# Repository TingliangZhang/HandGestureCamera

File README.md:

# HandGestureCamera

## BP相关

主控芯片及PCB上外围电路 约100 其中包括：

| 名称                    | 作用                | 估算BOM价格/RMB |
| ----------------------- | ------------------- | --------------- |
| ESP32-WROOM             | 主控兼Wifi+蓝牙通信 | 13              |
| 网络分析仪或FPGA替代品  | 测量阻抗            | 20-100          |
| 高频多路选通器          | 两两选通电极        | 5x2             |
| PCB SMT及供电等部分元件 | 集成化              | 10              |

电极及外壳代工 10 

物流及营销费用 10

## 肌电技术方案

测试仪器：[LCR/阻抗分析仪](https://www.hioki.cn/html/methods/power.html)

LCR是单一频率下的阻抗分析仪

复现一款PCB：

[AD5933](https://www.analog.com/cn/products/ad5933.html)+[ADG1608](https://www.analog.com/cn/products/adg1608.html) 

AD5933

I2C通信

ADG1608

EN高电平使能 A2A1A0选通 每片占用4pin数字输出

Arduino采用[Seeed XIAO RP2040](https://www.seeedstudio.com/XIAO-RP2040-v1-0-p-5026.html)

3+3+EN数字输出，2xI2C，2xUART，正好占满qwq

或者希望引脚宽裕一点直接用[Raspberry Pi Pico](https://www.raspberrypi.com/documentation/microcontrollers/raspberry-pi-pico.html)，还更便宜，但是只有3.3V，PCB这边我I2C用的5V

但是由于RP2040 MCU电压就是3.3，其实XIAO的I2C也不一定能work，Arduino板同理

ADG1608额定电源电压：±15 V/12 V/±5 V，3 V逻辑兼容输入，目前PCB设计可能有问题，单5V输入可能会导致开关出错

想用CD74HC4051这种 8:1, 1-channel analog mutliplexer 单通道模拟多路复用器

首先绝对不能用TMUX1308这种数字多路复用器

其他要考虑的事情：

其次驱动电压

内阻

支持的最大电流

备选项包括：ADG1408YRUZ、CD4051B

参考文档 [ 多路复用器和信号开关词汇表 (Rev. B)](https://www.ti.com.cn/cn/lit/pdf/zhcaad5) 中的解释，可以知道，其实8：1双通道模拟多路复用器更适合，如[CD4097B](https://www.ti.com/product/CD4097B) - 20-V, 8:1 differential, 1-channel analog multiplexer，或 [MUX36D08](https://www.ti.com.cn/product/cn/MUX36D08) - 1pA 开路泄漏电流、36V、8:1 精密模拟多路复用器

在TI的[模拟开关 & 多路复用器](https://www.ti.com.cn/zh-cn/switches-multiplexers/analog/overview.html)中可以挑选，

[TMUX1108](https://www.ti.com.cn/product/cn/TMUX1108) - 3pA 导通状态泄漏电流、5V、±2.5V、8:1、单通道精密多路复用器

[TMUX1208](https://www.ti.com.cn/product/cn/TMUX1208) - 具有 1.8V 输入逻辑的 5V、8:1、单通道通用模拟多路复用器

[TMUX1308](https://www.ti.com.cn/product/cn/TMUX1308) - 具有 1.8V 逻辑电平控制的 5V、8:1、单通道通用多路复用器

最终选定：[TMUX1208](https://www.ti.com.cn/product/cn/TMUX1208) 或 [CD74HC4051](https://www.ti.com.cn/product/cn/CD74HC4051)

[CD74HC4051PWR](https://item.szlcsc.com/328685.html) jlc充足现货，可以优先，另购买平替[74HC4051M/TR SOP-16](https://item.szlcsc.com/520618.html)作为备用，但是封装不同，画两个不同的板子或在同一个板子上面画两个方案。

即[CD74HC4051PWR TSSOP-16](https://item.szlcsc.com/328685.html) + [74HC4051M/TR SOP-16](https://item.szlcsc.com/520618.html) 方案

## Arduino

[arduino-ad5933](https://github.com/mjmeli/arduino-ad5933)

用[Seed XIAO RP2040](https://wiki.seeedstudio.com/XIAO-RP2040/) with Arduino不行，没输出

用[ESP32-DevKitC](https://www.espressif.com/en/products/devkits/esp32-devkitc/overview) with Arduino行，一下子就跑通了，调高波特率到115200还贼快，一句话：ESP32牛逼

ESP32开发板接线：SCL-D22、SDA-D21，5V-VIN，GND-GND

Timer参考ESP32 Arduino Example中的ESP32-Timer-Repeat Timer例程，设置定时器

20220406 Debug了一下午，发现俩问题：写switch不写break、Enable电平搞错了。一句话我是傻子。。。

[CD74HC4051 数据表、产品信息和支持| 德州仪器TI.com.cn](https://www.ti.com.cn/product/cn/CD74HC4051) Debug，发现是低电平Enable，之前板子画错了qwq，现在接了一根GND到板子的EN上面，就好了

| ENABLE | S2   | S1   | S0   | ON CHANNEL |
| ------ | ---- | ---- | ---- | ---------- |
| L      | L    | L    | L    | A0         |
| L      | L    | L    | H    | A1         |
| L      | L    | H    | L    | A2         |
| L      | L    | H    | H    | A3         |
| L      | H    | L    | L    | A4         |
| L      | H    | L    | H    | A5         |
| L      | H    | H    | L    | A6         |
| L      | H    | H    | H    | A7         |
| H      | X    | X    | X    | None       |

注意编码中S2是最高位！！！第一版本出错是因为编码反了。

gg，刚刚静电电了一下手环，我怀疑MUX被电坏了或者是芯片完蛋了。。。Z变成了3-4w，最低1w

刚刚换成Mega2560测试了一圈，感觉还是采样频率的问题，Frequency越小，比如1kHz，扫描速度越慢。现在调成10kHz甚至20kHz就好很多了，累加一次，准确度目前看是够用的

## Python数据读取和可视化

用[JupyterLab](https://jupyter.org/)+[Plotly Python Graphing Library](https://plotly.com/python/)做可交互的实时数据可视化。

Pyserial读取收到的数据，以下为数据格式的说明

```
0:1
90: R=348/I=1914  |Z|=102512.95
100: R=102/I=2118  |Z|=93806.21
Frequency sweep complete!
```

A:B 从0-8端口中选通两个，测量这两个端口之间的阻抗。

100: / 101: 当前扫描频率，单位为kHz

R/I  中间原始数据的实部虚部

|Z| 测得的阻抗数据，可以进行归一化，由于短路情况下|Z|= REF_RESIST 即10000

想要更简洁的数据，可以修改ino文件，比如0:1 10000 \n

由于AD5933扫描速度的限制，一次扫描约耗时1.5s

Plotly Python Open Source Graphing Library 示例

[2D Histograms](https://plotly.com/python/2D-Histogram/) 二维直方图表示可视化后的二维空间分布

[Histograms](https://plotly.com/python/histograms/) 为原始数据的可视化直方图，28个数据按照两两之间距离从小到大有序排列

[ML Regression](https://plotly.com/python/ml-regression/) 训练过程和效率可视化

## 应用方向

AR手势识别

手语识别

健康管理：

Use [Skulpt](https://www.skulpt.me/) to measure your body fat percentage and get a personalized workout plan to burn fat and build muscle.

## 手势识别相机手环

使用两个位于手表位置的前视摄像头实时识别手势

用于AR设备的手势识别辅助

技术难点：

受限于手腕视角，只能看到骨骼突起和肌肉拉伸，以及偶尔出现的手指，做模式识别可能会比较困难，不同人可能要单独标定。

动态手势复杂度高，手指关节很多

手势数据集较少，我们这一特定的场景还需要单独采集数据集

手环所在位置一定程度上会影响识别的结果

技术方案：

数据集获取使用Leapmotion提取手势关节数据，结合两个摄像头采集到的信息作为训练集。

1.多模态输入

将若干帧光流图像连接在单张彩色图像的通道维度上，将其作为深度网络的输入，使得输入数据中既包含空间信息又携带时序信息，以此来实现动态手势识别

一个序列不同的模态携带不同的信息，RGB图片包含丰富的颜色和纹理信息，深度图片包含物体的轮廓和深度信息，光流分别描述了像素在x方向与y方向的运动信息。这些数据在信息描述上具有互补性，将它们融合起来，能够有效弥补单一模态数据的局限性。

基于RGB 序列和Depth序列和Flow序列的融合特征进行动态手势识别

2.手部检测器预处理

融合彩色和深度数据的双通道Faster R-CNN手部检测框架

3.基于人工特征的机器学习算法的动态手势建模

经典的方法有规整动态时间(Dynamic Time Warping, DTW)算法、隐马尔科夫模型(Hidden Markov Model, HMM)

这部分可以视能否直接得到手部数据来决定做不做

参考

https://image.hanspub.org/Html/19-1541767_35738.htm

https://www.hindawi.com/journals/tswj/2014/267872/

## 新的肌电方法

Tomo: Wearable, Low-Cost Electrical Impedance Tomography for Hand Gesture Recognition

https://dl.acm.org/doi/10.1145/2807442.2807480

金属电极+双选择器+网络分析仪芯片+ESP32+小锂电

https://www.youtube.com/watch?v=FqgwBc7cGZ8

能不能做连续的

下垂和举起手是否能够鲁棒识别

其他身体部分，比如袜子

这一作老哥后来还做了手表周围的另一只手的触摸识别

https://dl.acm.org/doi/10.1145/2984511.2984568

以及手指是否摸到皮肤的识别

https://dl.acm.org/doi/10.1145/3332165.3347869

和一些导电物体周围贴上电极的识别

https://dl.acm.org/doi/10.1145/3025453.3025842

## 新的想法-手语识别

目标是识别中文手语，关于中文手语的科普参考 [回形针Vol.154 手语的秘密](https://www.youtube.com/watch?v=vpkHTLhuDqg)

发现手语包括手部动作、肢体语言、面部表情

目前ASL图像识别方面做的比较好的是国外的[SignAll](https://www.signall.us/)，看图片是一个Kinect2和俩Realsense D435i，还有一个铁架子打光+架设摄像头，使用者要戴上一个五彩斑斓的手套。国内则是[腾讯优图发布的AI手语翻译机](https://cloud.tencent.com/developer/article/1430241)通过单摄像头识别，但是看起来需要很高的算力，DEMO用的是外星人的笔记本。

其实可以先做ABC的识别：这个是一个很傻的一个一个字母翻译的网页[English to Sign Language (ASL) Translator](https://wecapable.com/tools/text-to-sign-language-converter/)

[Hand Talk Translator](https://play.google.com/store/apps/details?id=br.com.handtalk)是逆向的转换，从文本到动漫人物动作的转换，国内类似产品是[搜狗AI开发平台手语数字人](https://ai.sogou.com/solution/signlanguage_digitalman/)

[手语也能机器翻译了！机器学习手势识别功能了解一下](https://blog.51cto.com/u_14815220/3451551) 华为机器学习（ML Kit）提供手部关键点识别服务，可用于手语识别。手部关键点识别服务能识别手部21个关键点，通过每个手指的方向和手语规则作比较去找手语字母表。

后期可以做根据国家通用手语词典来做8k+的词组识别。

申专利、发顶会、打比赛

## 竞品

[Tenzr: A Fun and Efficient Way to Regain Mobility and Function](https://tenzrhealth.com/) 主打手腕康复，就离谱，感觉是智商税，技术方案是IMU

[TENZR, the next generation gesture recognition wrist-band for VR AR, to be presented at CES 2018](https://www.prnewswire.com/news-releases/tenzr-the-next-generation-gesture-recognition-wrist-band-for-vr-ar-to-be-presented-at-ces-2018-300572362.html)

这个报告里面的BioInteractive Technologies Inc.和上一个是同一家智商税公司，所以这个只是个想法，没做。

[Myo Gesture Control Armband review](https://www.digitaltrends.com/pc-accessory-reviews/myo-gesture-control-armband-review/) EMG原理，很多年前就比较完善了，但是已经停产了xs，估计无了

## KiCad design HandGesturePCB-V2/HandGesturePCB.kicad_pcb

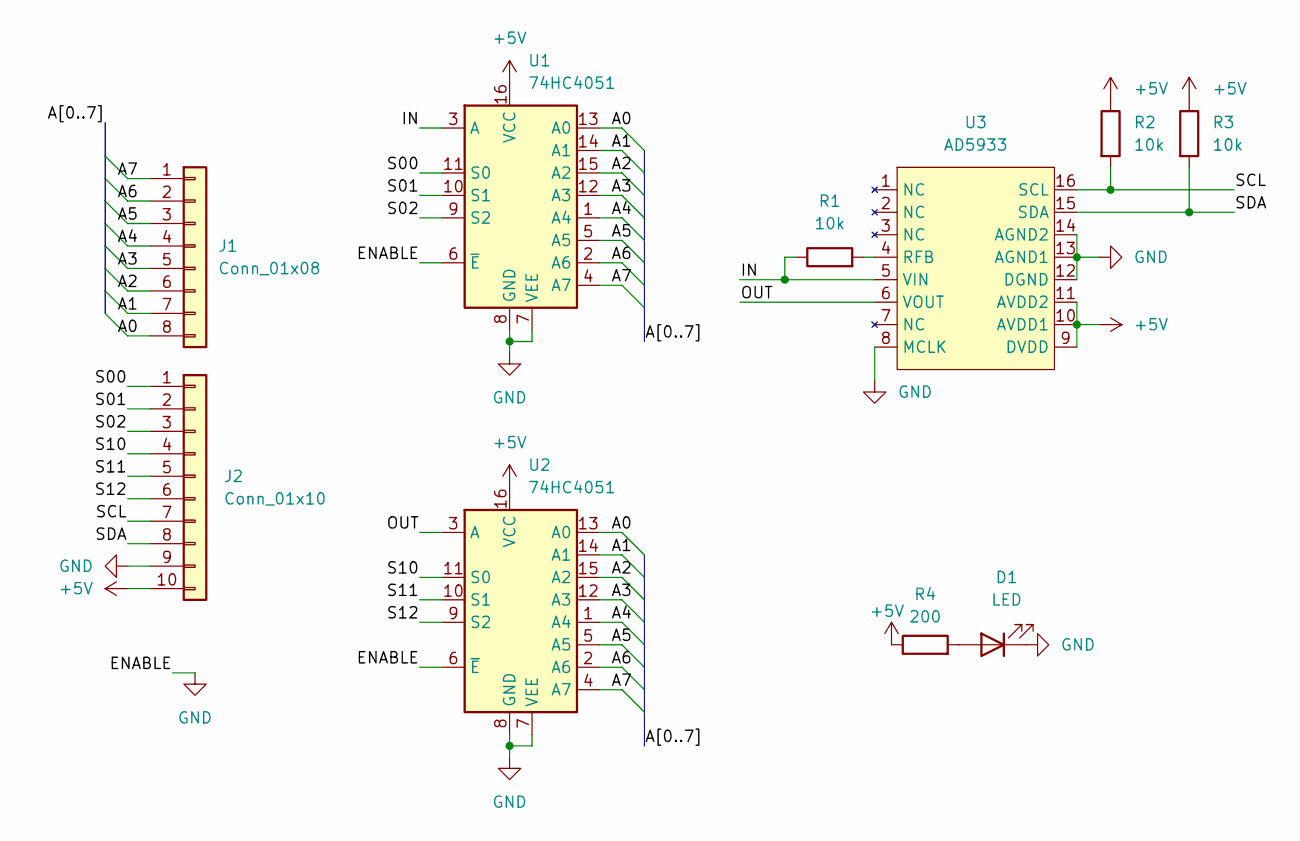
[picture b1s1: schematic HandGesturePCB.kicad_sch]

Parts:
D1: LED; LED_0603_1608Metric
J1: Conn_01x08; PinHeader_1x08_P2.54mm_Horizontal
J2: Conn_01x10; PinHeader_1x10_P2.54mm_Horizontal
R1, R2, R3: 10k; R_0603_1608Metric
R4: 200; R_0603_1608Metric
U1, U2: 74HC4051; TSSOP-16_4.4x5mm_P0.65mm
U3: AD5933; SSOP-16_5.3x6.2mm_P0.65mm

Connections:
+5V: J2.10, R2.1, R3.1, R4.1, U1.16 (VCC), U2.16 (VCC), U3.9 (DVDD), U3.10 (AVDD1), U3.11 (AVDD2)
/A0: J1.8, U1.13 (A0), U2.13 (A0)
/A1: J1.7, U1.14 (A1), U2.14 (A1)
/A2: J1.6, U1.15 (A2), U2.15 (A2)
/A3: J1.5, U1.12 (A3), U2.12 (A3)
/A4: J1.4, U1.1 (A4), U2.1 (A4)
/A5: J1.3, U1.5 (A5), U2.5 (A5)
/A6: J1.2, U1.2 (A6), U2.2 (A6)
/A7: J1.1, U1.4 (A7), U2.4 (A7)
/IN: R1.1, U1.3 (A), U3.5 (VIN)
/OUT: U2.3 (A), U3.6 (VOUT)
/S00: J2.1, U1.11 (S0)
/S01: J2.2, U1.10 (S1)
/S02: J2.3, U1.9 (S2)
/S10: J2.4, U2.11 (S0)
/S11: J2.5, U2.10 (S1)
/S12: J2.6, U2.9 (S2)
/SCL: J2.7, R2.2, U3.16 (SCL)
/SDA: J2.8, R3.2, U3.15 (SDA)
GND: D1.1 (K), J2.9, U1.6 (~E), U1.7 (VEE), U1.8 (GND), U2.6 (~E), U2.7 (VEE), U2.8 (GND), U3.8 (MCLK), U3.12 (DGND), U3.13 (AGND1), U3.14 (AGND2)
unnamed: D1.2 (A), R4.2
unnamed: R1.2, U3.4 (RFB)

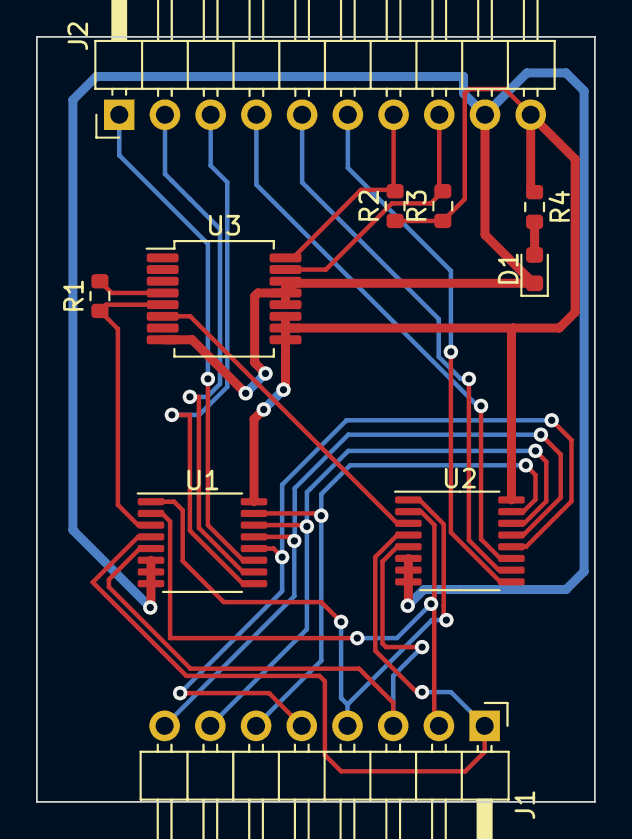
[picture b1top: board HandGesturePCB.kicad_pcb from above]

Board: 2 copper layers, 31.0 x 42.5 mm, 10 parts (0 on the bottom side), 22 nets.

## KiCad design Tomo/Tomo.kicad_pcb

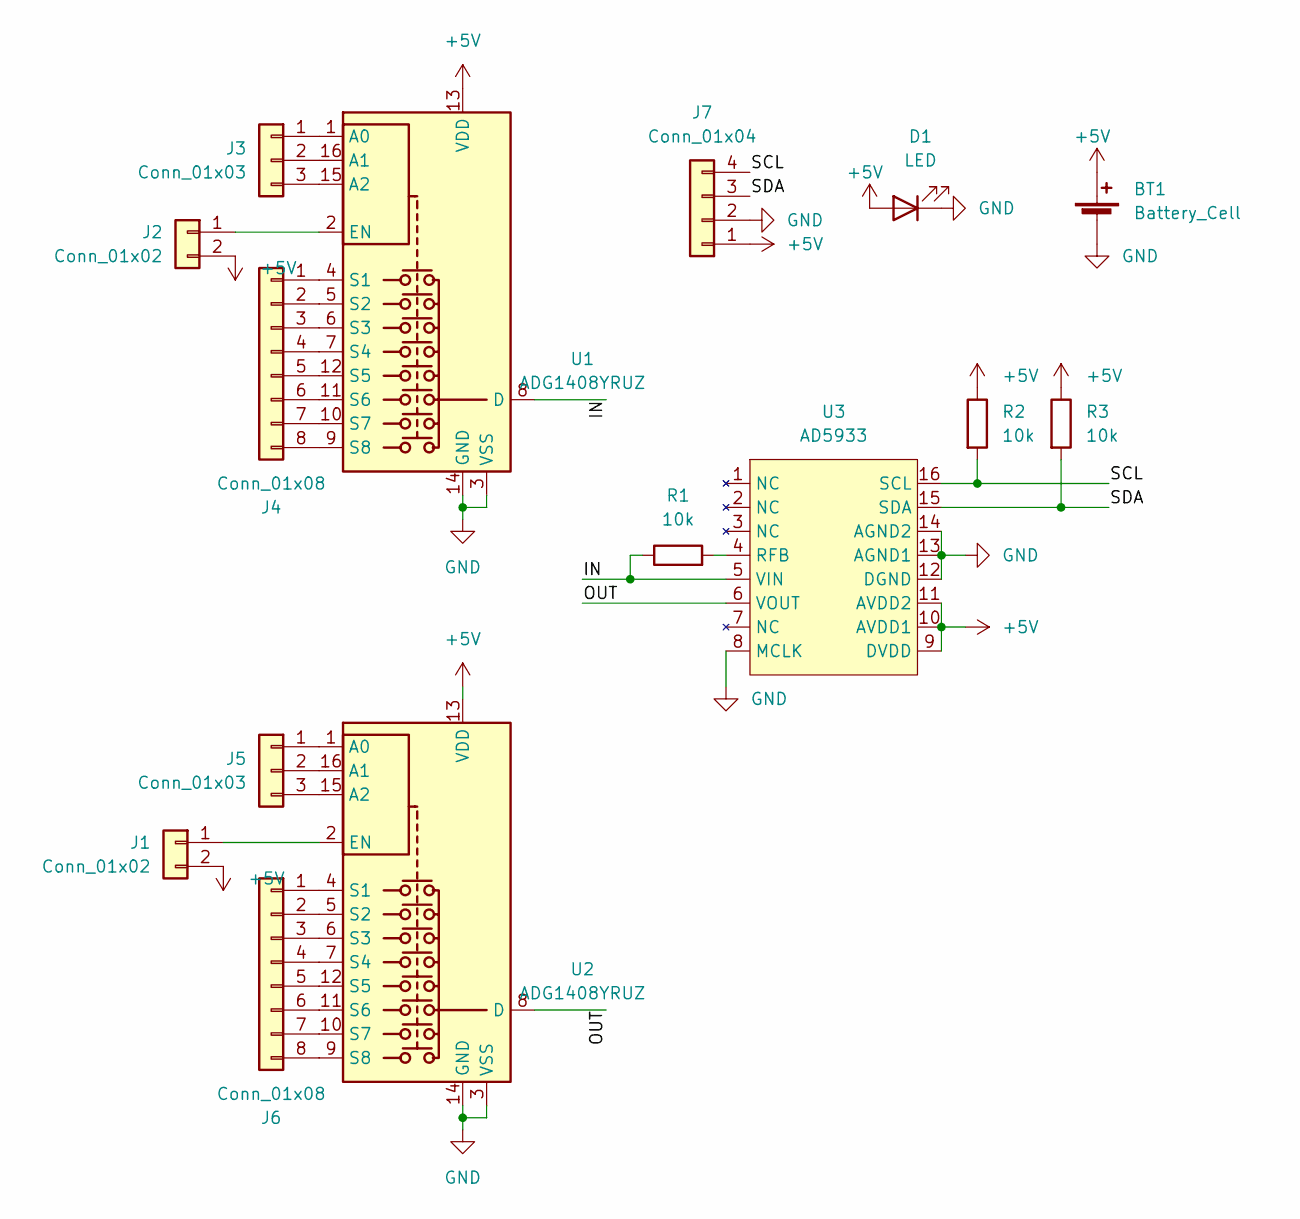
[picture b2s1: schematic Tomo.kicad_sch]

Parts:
BT1: Battery_Cell; PinHeader_1x02_P2.54mm_Vertical
D1: LED
J1, J2: Conn_01x02; PinSocket_1x02_P2.54mm_Vertical
J3, J5: Conn_01x03; PinSocket_1x03_P2.54mm_Vertical
J4, J6: Conn_01x08; PinSocket_1x08_P2.54mm_Vertical
J7: Conn_01x04; PinHeader_1x04_P2.54mm_Vertical
R1, R2, R3: 10k; R_0603_1608Metric
U1, U2: ADG1408YRUZ; TSSOP-16_4.4x5mm_P0.65mm
U3: AD5933; SSOP-16_5.3x6.2mm_P0.65mm

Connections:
+5V: BT1.1 (+), D1.2 (A), J1.2, J2.2, J7.1, R2.1, R3.1, U1.13 (VDD), U2.13 (VDD), U3.9 (DVDD), U3.10 (AVDD1), U3.11 (AVDD2)
/IN: R1.1, U1.8 (D), U3.5 (VIN)
/OUT: U2.8 (D), U3.6 (VOUT)
/SCL: J7.4, R2.2, U3.16 (SCL)
/SDA: J7.3, R3.2, U3.15 (SDA)
GND: BT1.2 (-), D1.1 (K), J7.2, U1.3 (VSS), U1.14 (GND), U2.3 (VSS), U2.14 (GND), U3.8 (MCLK), U3.12 (DGND), U3.13 (AGND1), U3.14 (AGND2)
unnamed: J1.1, U2.2 (EN)
unnamed: J2.1, U1.2 (EN)
unnamed: J3.1, U1.1 (A0)
unnamed: J3.2, U1.16 (A1)
unnamed: J3.3, U1.15 (A2)
unnamed: J4.1, U1.4 (S1)
unnamed: J4.2, U1.5 (S2)
unnamed: J4.3, U1.6 (S3)
unnamed: J4.4, U1.7 (S4)
unnamed: J4.5, U1.12 (S5)
unnamed: J4.6, U1.11 (S6)
unnamed: J4.7, U1.10 (S7)
unnamed: J4.8, U1.9 (S8)
unnamed: J5.1, U2.1 (A0)
unnamed: J5.2, U2.16 (A1)
unnamed: J5.3, U2.15 (A2)
unnamed: J6.1, U2.4 (S1)
unnamed: J6.2, U2.5 (S2)
unnamed: J6.3, U2.6 (S3)
unnamed: J6.4, U2.7 (S4)
unnamed: J6.5, U2.12 (S5)
unnamed: J6.6, U2.11 (S6)
unnamed: J6.7, U2.10 (S7)
unnamed: J6.8, U2.9 (S8)
unnamed: R1.2, U3.4 (RFB)

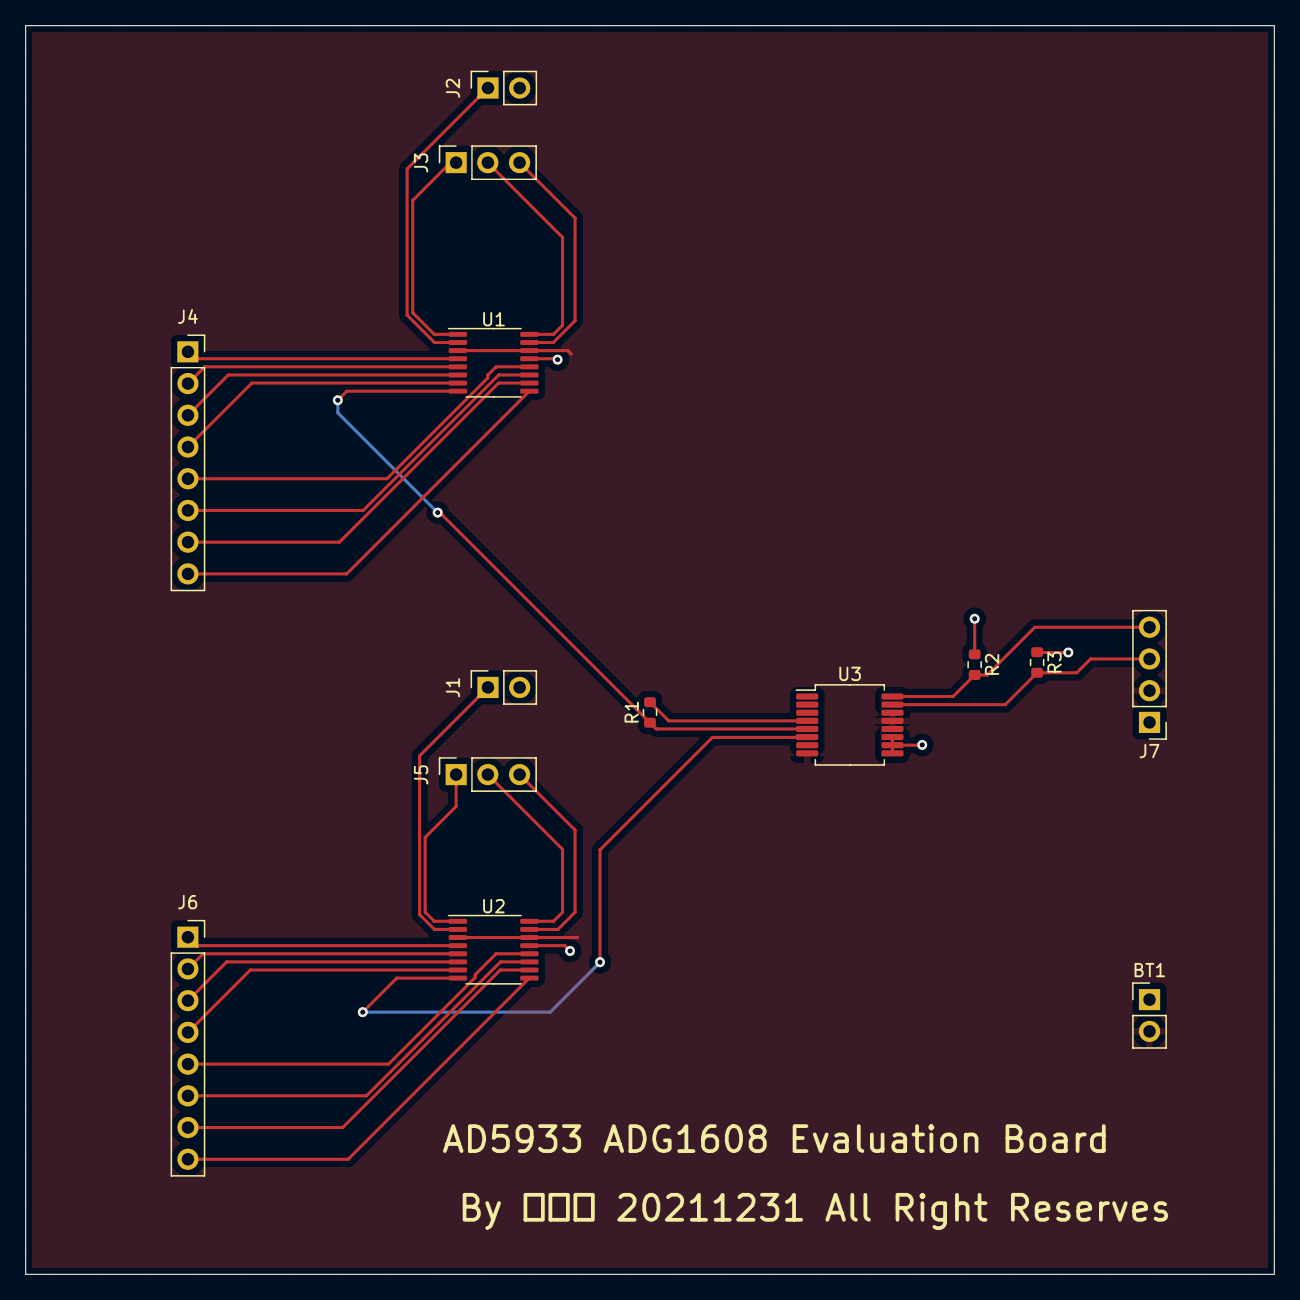
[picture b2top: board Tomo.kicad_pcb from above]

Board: 2 copper layers, 100.0 x 100.0 mm, 14 parts (0 on the bottom side), 31 nets.

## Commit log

2021-12-31 PCB Tomo
2021-12-31 TomoV1
2022-02-24 Datasheet
2022-03-13 pcb new ini
2022-03-14 beginLayout
2022-03-14 Finish
2022-03-16 清关材料
2022-04-06 debug break
2022-04-06 静电电了一下
2022-04-08 ESP32-C3
2022-04-09 format output
2022-04-12 PCB-V2+Pic
2022-04-15 Jupyter
